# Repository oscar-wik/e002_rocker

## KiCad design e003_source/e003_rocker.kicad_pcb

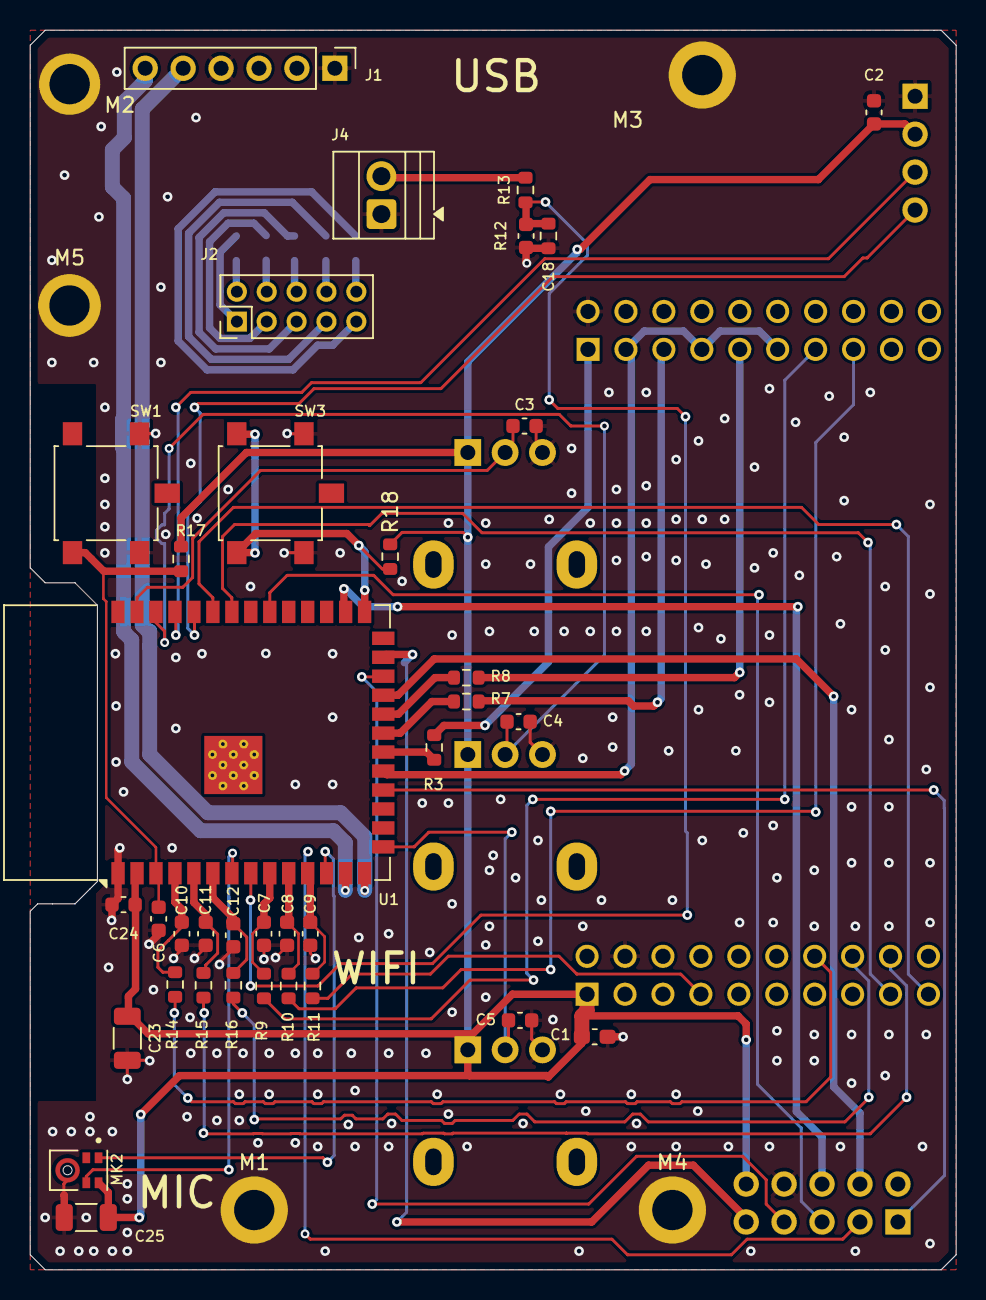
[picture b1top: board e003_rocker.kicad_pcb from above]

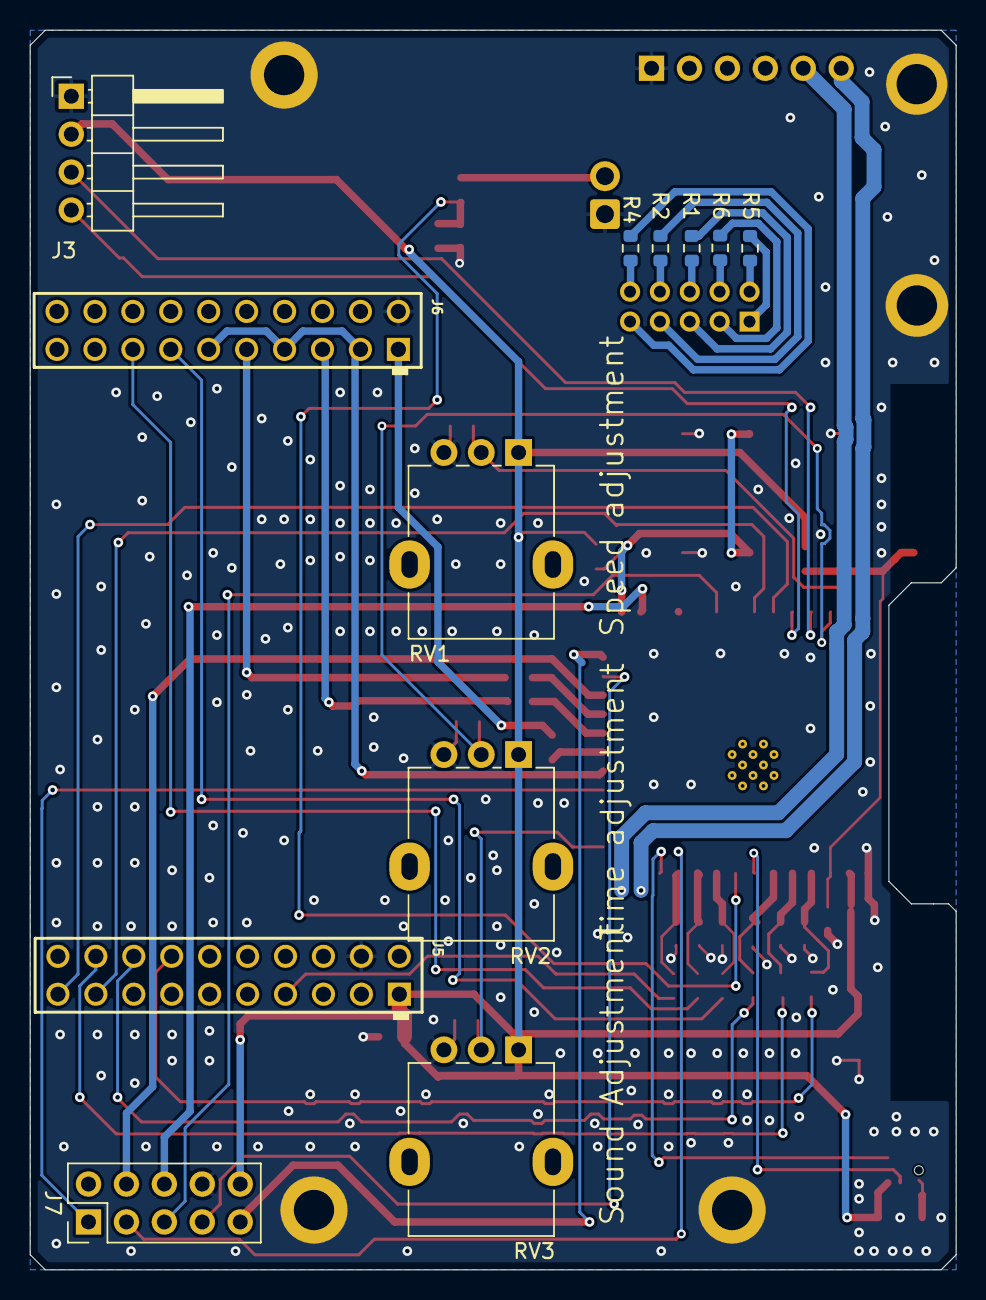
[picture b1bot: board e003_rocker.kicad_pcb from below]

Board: 2 copper layers, 62.0 x 83.0 mm, 53 parts (12 on the bottom side), 52 nets.

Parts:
C1: CL10A105KB8NNNC; C_0603_1608Metric_Pad1.08x0.95mm_HandSolder
C2, C3, C4, C5: 100NF_0201_10V_X7R; C_0603_1608Metric
C6, C18, C24: 1UF 0603 16V X7R; C_0603_1608Metric
C7, C8, C9, C10, C11, C12: 220PF 0603 50V C0G; C_0603_1608Metric
C23: 10UF_1206_35V_X5R; C_1206_3216Metric
C25: 100NF_0201_10V_X7R; C_1206_3216Metric
J1: Conn_01x06_Pin; PinHeader_1x06_P2.54mm_Vertical
J2: Conn_02x05_Odd_Even; PinHeader_2x05_P2.00mm_Vertical
J3: Conn_01x04; PinHeader_1x04_P2.54mm_Horizontal
J4: Conn_01x02_Pin; TerminalBlock_Xinya_XY308-2.54-2P_1x02_P2.54mm_Horizontal
J5, J6: SSQ-110-03-G-D; Samtec_SSQ-110-03-x-D
J7: Conn_02x05_Odd_Even; PinHeader_2x05_P2.54mm_Vertical
M1, M2, M3, M4, M5: CONN_M4_MOUNT; MountingHole_2.7mm_M2.5_ISO7380_Pad
MK2: IC_KNOWLES_SPH0141LM4H-1; MIC_KNOWLES_SPH0641LM4H-1
R1, R2, R4, R5, R6: 1K 0603; R_0603_1608Metric
R3, R7, R8, R9, R10, R11, R14, R15, R16: 100R 0603; R_0603_1608Metric
R12, R18: 10K 0603; R_0603_1608Metric
R13: 100K 0603; R_0603_1608Metric
R17: 5.6K 0603; R_0603_1608Metric
RV1, RV2, RV3: R_Potentiometer; Potentiometer_Alpha_RD901F-40-00D_Single_Vertical
SW1, SW3: BTN_OMRON_B3S-1100P; SW_SPST_B3S-1100
U1: ESP32-S3-WROOM-1-N8R2; ESP32-S3-WROOM-1

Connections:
+3V3: C1.1, C2.1, C23.1, C24.1, C25.1, J3.2, J5.1, J7.10, MK2.5 (VDD), R17.2, R18.2, RV1.1, RV2.1, RV3.1, U1.2 (3V3)
/DRV-HIZ_N: J6.3, J6.7, J6.11, U1.19 (IO11)
/DRV-INHA: J6.1, R3.2
/DRV-INHB: J6.5, R7.2
/DRV-INHC: J6.9, R8.2
/ESP-RXD: J3.4, U1.36 (RXD0)
/ESP-TXD: J3.3, U1.37 (TXD0)
/ESP_EN: C6.1, R17.1, SW1.1 (B), U1.3 (EN)
/ESP_IO0: R18.1, SW3.1 (B), U1.27 (IO0)
/GIO10: J7.1, U1.18 (IO10)
/GIO21: J7.4, U1.23 (IO21)
/GIO35: J7.6, U1.28 (IO35)
/GIO39: J7.5, U1.32 (IO39)
/GIO47: J7.7, U1.24 (IO47)
/GIO48: J7.9, U1.25 (IO48)
/HALL-A: J6.13, R9.2
/HALL-B: J6.15, R10.2
/HALL-C: J5.7, R11.2
/ISENS_A: J5.14, R14.1
/ISENS_B: J5.16, R16.1
/ISENS_C: J5.18, R15.1
/MIC_CLK: MK2.4 (CLOCK), U1.7 (IO7)
/MIC_DATA: MK2.1 (DATA), U1.12 (IO8)
/PD_5V: J2.10, R4.2
/PD_9V: J2.8, R2.2
/PD_12V: J2.6, R1.2
/PD_15V: J2.4, R6.2
/PD_20V: J2.2, R5.2
/POT_MIC: C5.1, RV3.2, U1.15 (IO3)
/POT_SPEED: C3.1, RV1.2, U1.39 (IO1)
/POT_TIME: C4.1, RV2.2, U1.38 (IO2)
/USB_N: J1.6, U1.13 (IO19)
/USB_P: J1.5, U1.14 (IO20)
/nFAULT: J5.19, U1.35 (IO42)
/nSLEEP: J5.17, U1.34 (IO41)
GND: C1.2, C2.2, C3.2, C4.2, C5.2, C6.2, C7.2, C8.2, C9.2, C10.2, C11.2, C12.2, C18.2, C23.2, C24.2, C25.2, J1.1, J1.4, J3.1, J4.1, J5.4, J6.2, J7.8, M1.1, M2.1, M3.1, M4.1, M5.1, MK2.3_1 (GND), MK2.3_2 (GND), R12.1, RV1.3, RV2.3, RV3.3, SW1.2 (1), SW3.2 (1), U1.1 (GND), U1.40 (GND__1)
unnamed: J2.1, R5.1
unnamed: J2.3, R6.1
unnamed: J2.5, R1.1
unnamed: J2.7, R2.1
unnamed: J2.9, R4.1
unnamed: C10.1, R14.2, U1.4 (IO4)
unnamed: C11.1, R15.2, U1.5 (IO5)
unnamed: C12.1, R16.2, U1.6 (IO6)
unnamed: R3.1, U1.20 (IO12)
unnamed: R7.1, U1.21 (IO13)
unnamed: R8.1, U1.22 (IO14)
unnamed: C7.1, R9.1, U1.9 (IO16)
unnamed: C8.1, R10.1, U1.10 (IO17)
unnamed: C9.1, R11.1, U1.11 (IO18)
VBUS: J4.2, R13.2
VBUS_SENSE: C18.1, R12.2, R13.1, U1.8 (IO15)

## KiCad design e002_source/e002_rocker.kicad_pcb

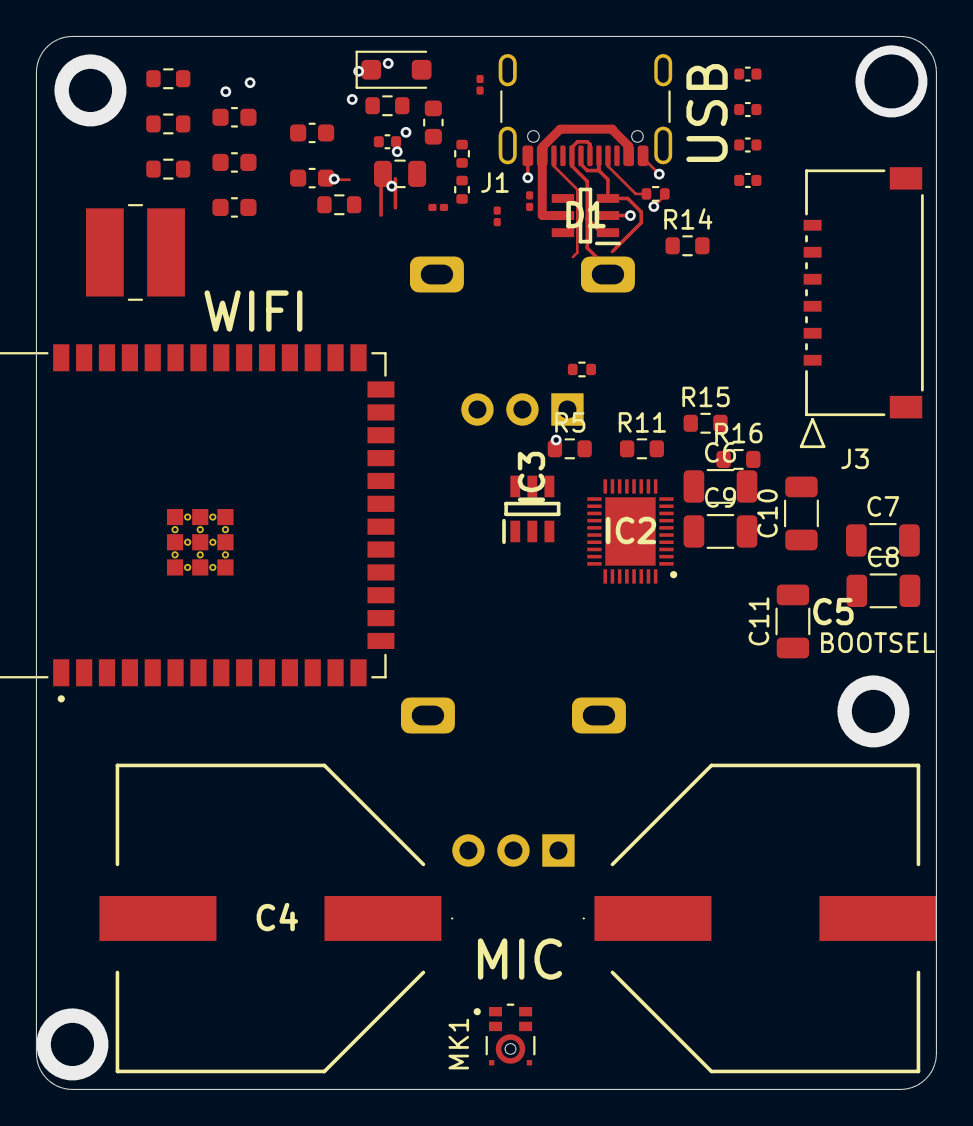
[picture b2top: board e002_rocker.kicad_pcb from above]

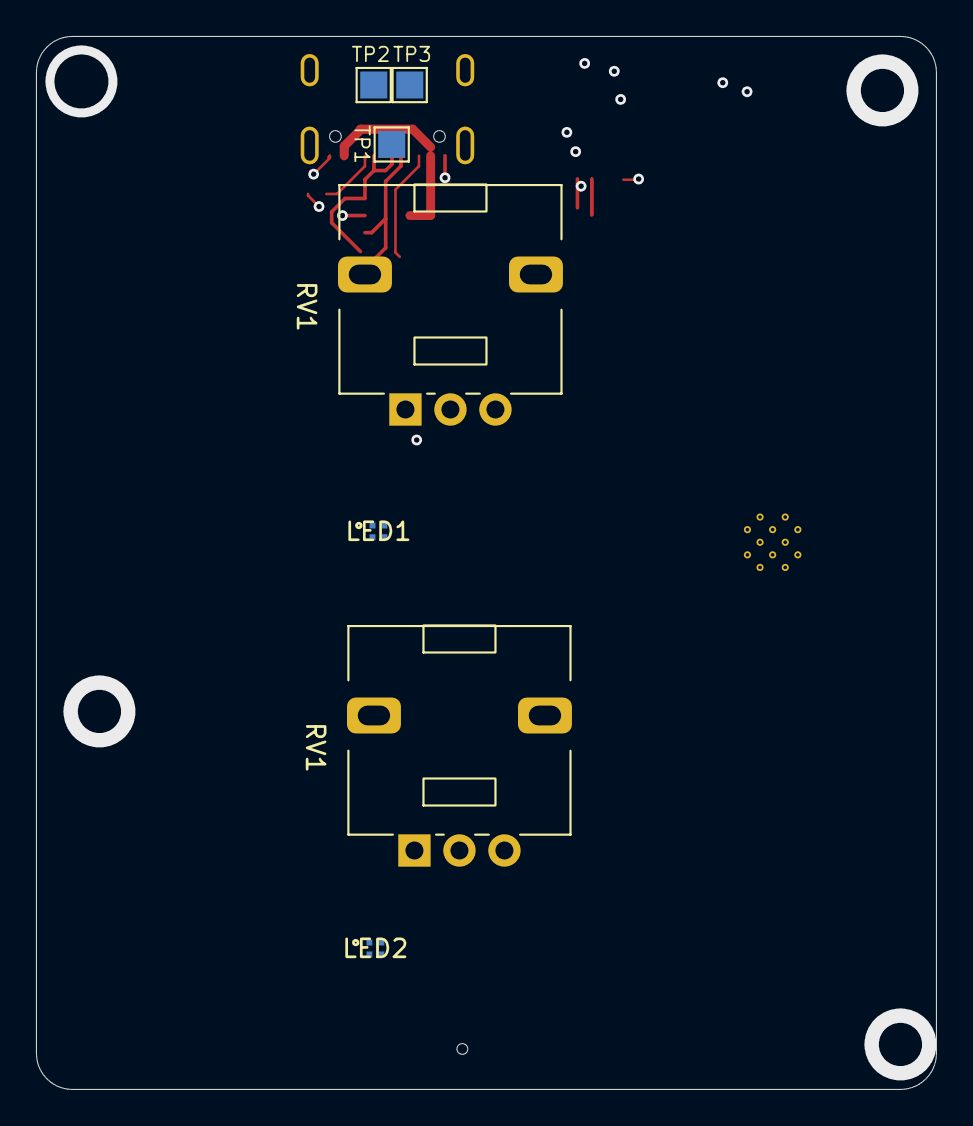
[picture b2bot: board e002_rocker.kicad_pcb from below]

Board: 2 copper layers, 50.0 x 58.5 mm, 54 parts (7 on the bottom side), 33 nets.

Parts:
C1: 4.7UF 0402 10V X7R; C_0402_1005Metric
C2: 1n; C_0201_0603Metric
C3: 10UF_0805_16V_X7R; C_0805_2012Metric
C4, C5: CAPP_PANASONIC_EEV-FK1E222M; CAPP_PANASONIC_EEEFK0J682AM
C6, C7, C8, C9, C10, C11: 10UF_1206_35V_X5R; C_1206_3216Metric
C12, C13, C14: 100NF 0402 25V X7R; C_0402_1005Metric
C15: 1UF 0603 16V X7R; C_0603_1608Metric
C16: 4.7NF 0603 100V X7R; C_0603_1608Metric
C17: 2.2UF 0402 16V X5R; C_0402_1005Metric
C18: 100NF_0201_10V_X7R; C_0201_0603Metric
C19, C20, C21: 47PF 0603 50V C0G; C_0603_1608Metric
D1: PRTR5V0U4D,125; SOT95P275X110-6N
D2: PMEG6010ELR; D_SOD-123F
IC2: DRV8317HREER; QFN40P400X500X80-37N-D
IC3: SOT95P280X125-6N
J1: USB_C_Receptacle_USB2.0_16P; USB_C_Receptacle_GCT_USB4105-xx-A_16P_TopMnt_Horizontal
J3: 5040500691; CONN_MOLEX_5040500691
L1: INDC_BEAD_BLM18AG601SN1D; L_0603_1608Metric
L3: INDC_TDK_VLCF5028T-220MR71-2; IND_TDK_VLCF5028T-220MR71-2
LED1, LED2: RGB; DIOD_CREE_UHD111A-FKA-C3K23E1L3VG5ZB3Z3
MK1: IC_MIC_TDK_MMICT5837-00-012
R1, R2: 5k1; R_0402_1005Metric
R3: 5k6; R_0201_0603Metric
R4: 10k; R_0201_0603Metric
R5, R6, R7, R8, R9, R10: 0R 0603; R_0603_1608Metric
R11, R14, R16: 330R 0603; R_0603_1608Metric
R12: 1.2M 0402; R_0402_1005Metric
R13: 680K 0402; R_0402_1005Metric
R15: 10K 0603; R_0603_1608Metric
RV1, RV1#2: R_Potentiometer; Potentiometer_Alps_RK09L_Single_Vertical
TP1, TP2, TP3: TestPoint; TestPoint_Pad_1.5x1.5mm
U1: ESP32-S3-WROOM-1-N8R2; IC_EXPIF_ESP32-S3-WROOM-1-N8R2

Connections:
+3V3: C3.1, L3.2, R5.2, R7.2, R9.2, R15.2, U1.2 (3V3)
/DRV-INHA: IC2.23 (INHA), U1.20 (IO12)
/DRV-INHB: IC2.25 (INHB), U1.21 (IO13)
/DRV-INHC: IC2.27 (INHC), U1.22 (IO14)
/DRV_AVDD: C17.1, IC2.22 (AVDD)
/ISENS_A: C21.1, R16.1, U1.4 (IO4)
/ISENS_B: C20.1, R14.1
/ISENS_C: C19.1, R11.1, U1.5 (IO5)
/MOTOR_A: IC2.11 (OUTA_1), IC2.12 (OUTA_2)
/MOTOR_B: IC2.14 (OUTB_1), IC2.15 (OUTB_2)
/MOTOR_C: IC2.17 (OUTC_1), IC2.18 (OUTC_2)
GND: C1.2, C2.2, C3.2, C4.2 (-), C5.2 (-), C6.2, C7.2, C8.2, C9.2, C10.2, C11.2, C12.2, C13.2, C14.2, C17.2, C18.2, C19.2, C20.2, C21.2, D1.2 (GND), IC2.10 (PGND_1), IC2.13 (PGND_2), IC2.16 (PGND_3), IC2.19 (PGND_4), IC2.21 (AGND), IC2.37 (GND), J1.A1 (GND), J1.A12 (GND), J1.B1 (GND), J1.B12 (GND), J1.S1 (SHIELD), R1.2, R2.2, R4.2, R6.1, R8.1, R10.1, R13.1, TP1.1, U1.1 (GND), U1.40 (GND__1), U1.41_1 (GND__2), U1.41_2 (GND__3), U1.41_3 (GND__4), U1.41_4 (GND__5), U1.41_5 (GND__6), U1.41_6 (GND__7), U1.41_7 (GND__8), U1.41_8 (GND__9), U1.41_9 (GND__10)
GPIO24: R3.2, R4.1
unnamed: C4.1 (+), C5.1 (+), C6.1, C7.1, C8.1, C9.1, C10.1, C11.1, C13.1, C14.1, C15.1, IC2.7 (VIN_AVDD), IC2.8 (VM_1), IC2.9 (VM_2), IC2.20 (VM_3)
unnamed: C15.2, IC2.6 (CP)
unnamed: C16.1, IC2.5 (CPH)
unnamed: C16.2, IC2.4 (CPL)
unnamed: C12.1, IC2.33 (CSAREF)
unnamed: IC2.29 (GAIN), R5.1, R6.2
unnamed: IC2.31 (MODE), R9.1, R10.2
unnamed: IC2.2 (NFAULT), R15.1
unnamed: IC2.30 (SLEW), R7.1, R8.2
unnamed: IC2.36 (SOA), R16.2
unnamed: IC2.35 (SOB), R14.2
unnamed: IC2.34 (SOC), R11.2
unnamed: IC3.6 (SW), L3.1
unnamed: C1.1, IC3.5 (VIN), L1.2
unnamed: J1.A5 (CC1), R1.1
unnamed: J1.B5 (CC2), R2.1
USB_DM: D1.3 (I/O2), J1.A7 (D-), J1.B7 (D-), TP2.1
USB_DP: D1.1 (I/O1), J1.A6 (D+), J1.B6 (D+), TP3.1
VBUS: C2.1, D1.5 (VCC), D2.2 (A), J1.A4 (VBUS), J1.A9 (VBUS), J1.B4 (VBUS), J1.B9 (VBUS), R3.1, R12.2
VBUS_SENSE: C18.1, R12.1, R13.2

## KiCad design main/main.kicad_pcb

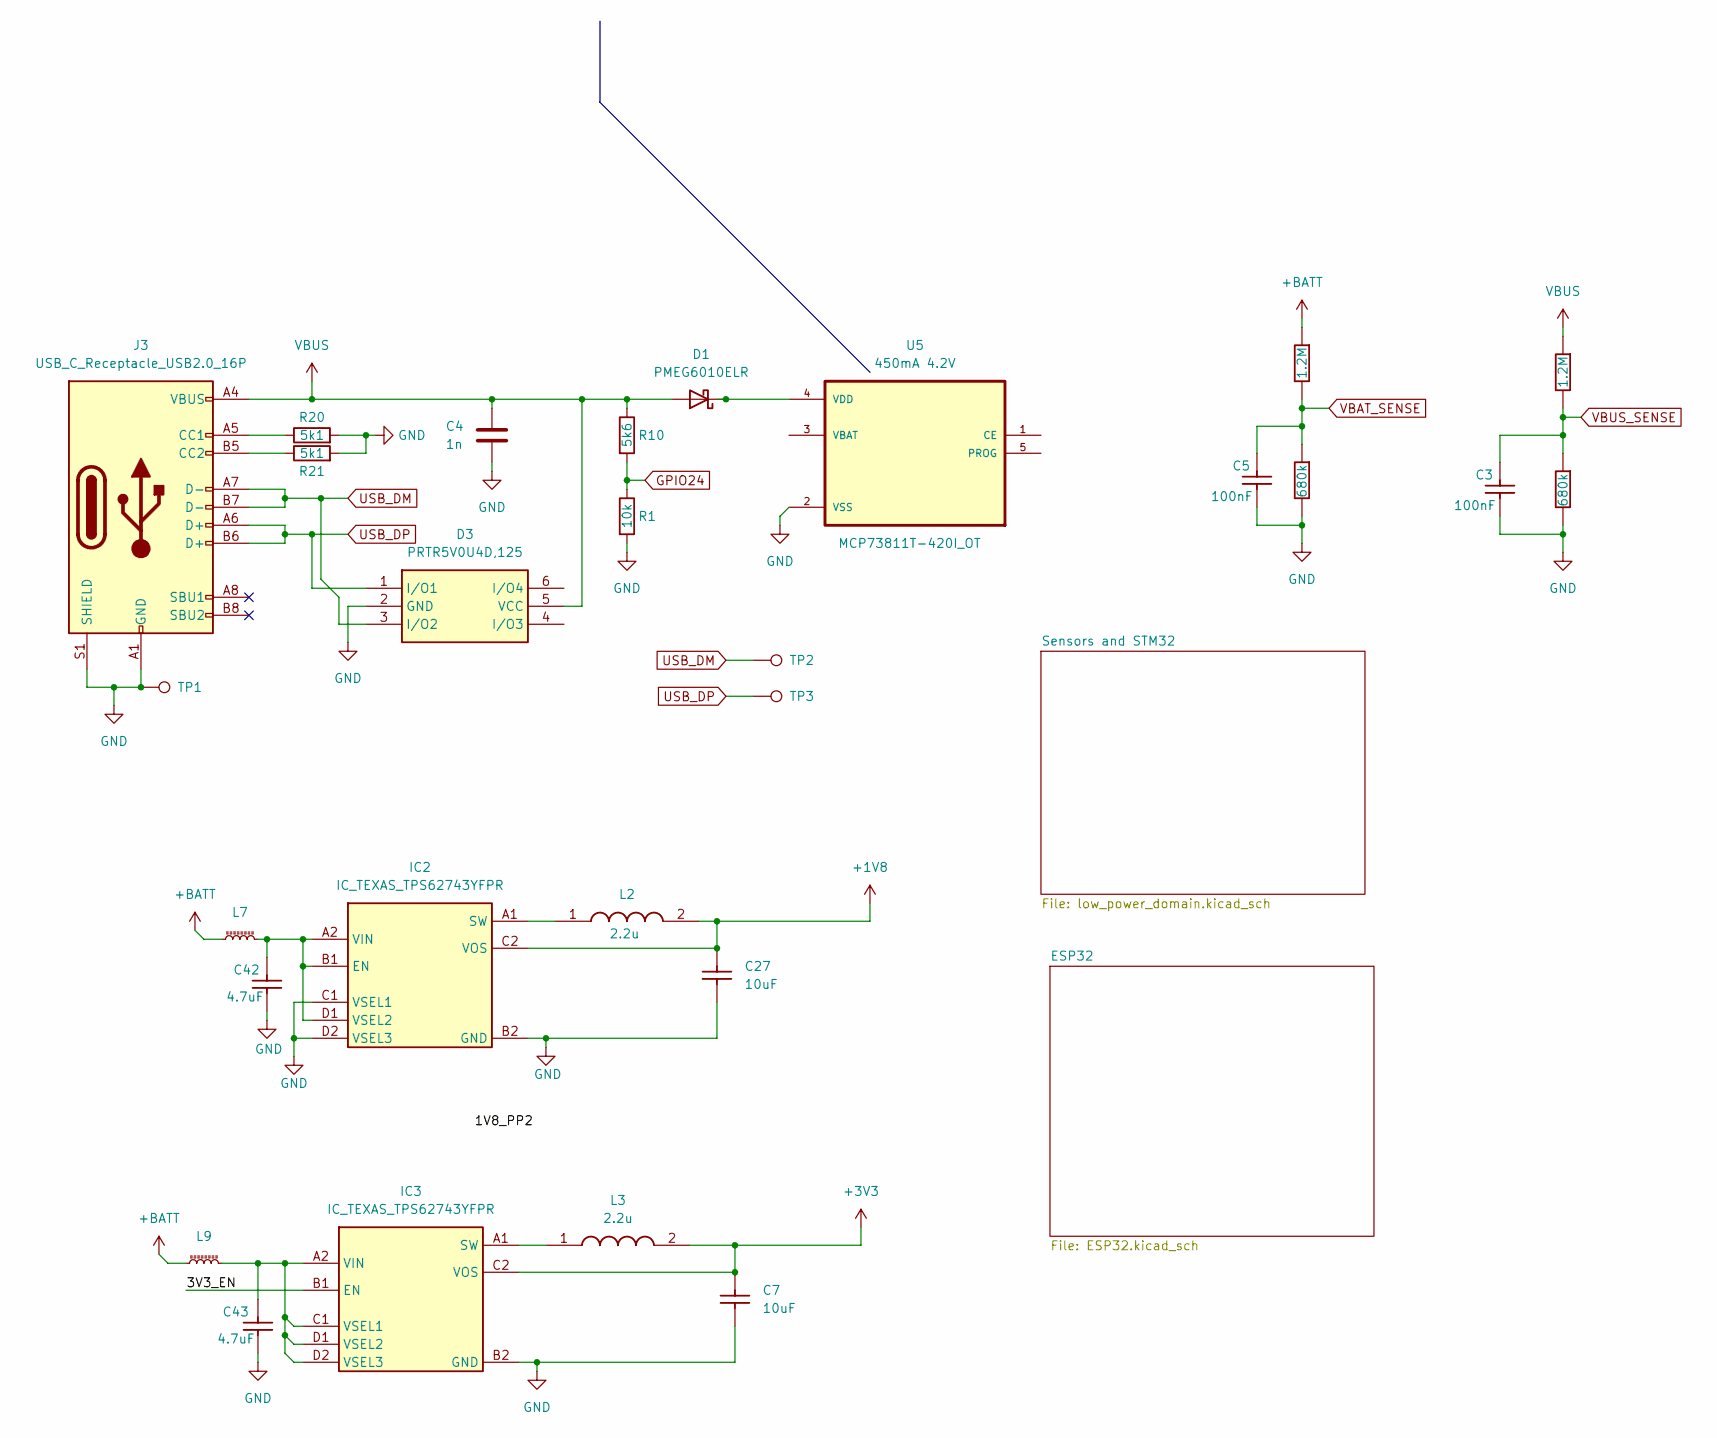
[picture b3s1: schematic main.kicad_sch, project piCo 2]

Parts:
C3, C5: 100NF_0201_10V_X7R; C_0201_0603Metric; Voltage 0V
C4: 1n; C_0201_0603Metric
C7, C27: 10UF_0805_16V_X7R; C_0805_2012Metric
C42, C43: 4.7UF 0402 10V X7R; C_0402_1005Metric; Voltage 0V
D1: PMEG6010ELR; D_SOD-123F
D3: PRTR5V0U4D,125; SOT95P275X110-6N; mpn Nexperia
IC2, IC3: IC_TEXAS_TPS62743YFPR; BGA8C40P2X4_87X156X53; mpn TPS627431YFPR
J3: USB_C_Receptacle_USB2.0_16P; USB_C_Receptacle_GCT_USB4105-xx-A_16P_TopMnt_Horizontal
L2, L3: 2.2u; IND_MURATA_DFE201610P-2R2M=P2; mpn DFE201610P-2R2M=P2
L7, L9: INDC_BEAD_BLM18AG601SN1D; L_0603_1608Metric; mpn BLM18AG601SN1D
R1: 10k; R_0201_0603Metric
R5, R7: 1.2M 0402; R_0402_1005Metric
R6, R9: 680K 0402; R_0402_1005Metric
R10: 5k6; R_0201_0603Metric
R20, R21: 5k1; R_0402_1005Metric
TP1, TP2, TP3: TestPoint; TestPoint_Pad_1.5x1.5mm
U5: 450mA 4.2V; SOT95P280X145-5N; mpn MCP73811T-420I_OT

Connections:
+1V8: C27.1, IC2.C2 (VOS), L2.2; also elsewhere on the board
+3V3: C7.1, IC3.C2 (VOS), L3.2; also elsewhere on the board
+BATT: L7.1, L9.1, R7.2; also elsewhere on the board
/3V3_EN: IC3.B1 (EN)
GND: C3.2, C4.2, C5.2, C7.2, C27.2, C42.2, C43.2, D3.2 (GND), IC2.B2 (GND), IC2.C1 (VSEL1), IC2.D2 (VSEL3), IC3.B2 (GND), J3.A1 (GND), J3.A12 (GND), J3.B1 (GND), J3.B12 (GND), J3.S1 (SHIELD), R1.2, R6.1, R9.1, R20.2, R21.2, TP1.1, U5.2 (VSS); also elsewhere on the board
GPIO24: R1.1, R10.2
unnamed: D1.1 (K), U5.4 (VDD)
unnamed: C42.1, IC2.A2 (VIN), IC2.B1 (EN), IC2.D1 (VSEL2), L7.2
unnamed: IC2.A1 (SW), L2.1
unnamed: IC3.A1 (SW), L3.1
unnamed: C43.1, IC3.A2 (VIN), IC3.C1 (VSEL1), IC3.D1 (VSEL2), IC3.D2 (VSEL3), L9.2
unnamed: J3.A5 (CC1), R20.1
unnamed: J3.B5 (CC2), R21.1
USB_DM: D3.3 (I/O2), J3.A7 (D-), J3.B7 (D-), TP2.1; also elsewhere on the board
USB_DP: D3.1 (I/O1), J3.A6 (D+), J3.B6 (D+), TP3.1; also elsewhere on the board
VBAT_SENSE: C5.1, R7.1, R9.2
VBUS: C4.1, D1.2 (A), D3.5 (VCC), J3.A4 (VBUS), J3.A9 (VBUS), J3.B4 (VBUS), J3.B9 (VBUS), R5.2, R10.1
VBUS_SENSE: C3.1, R5.1, R6.2

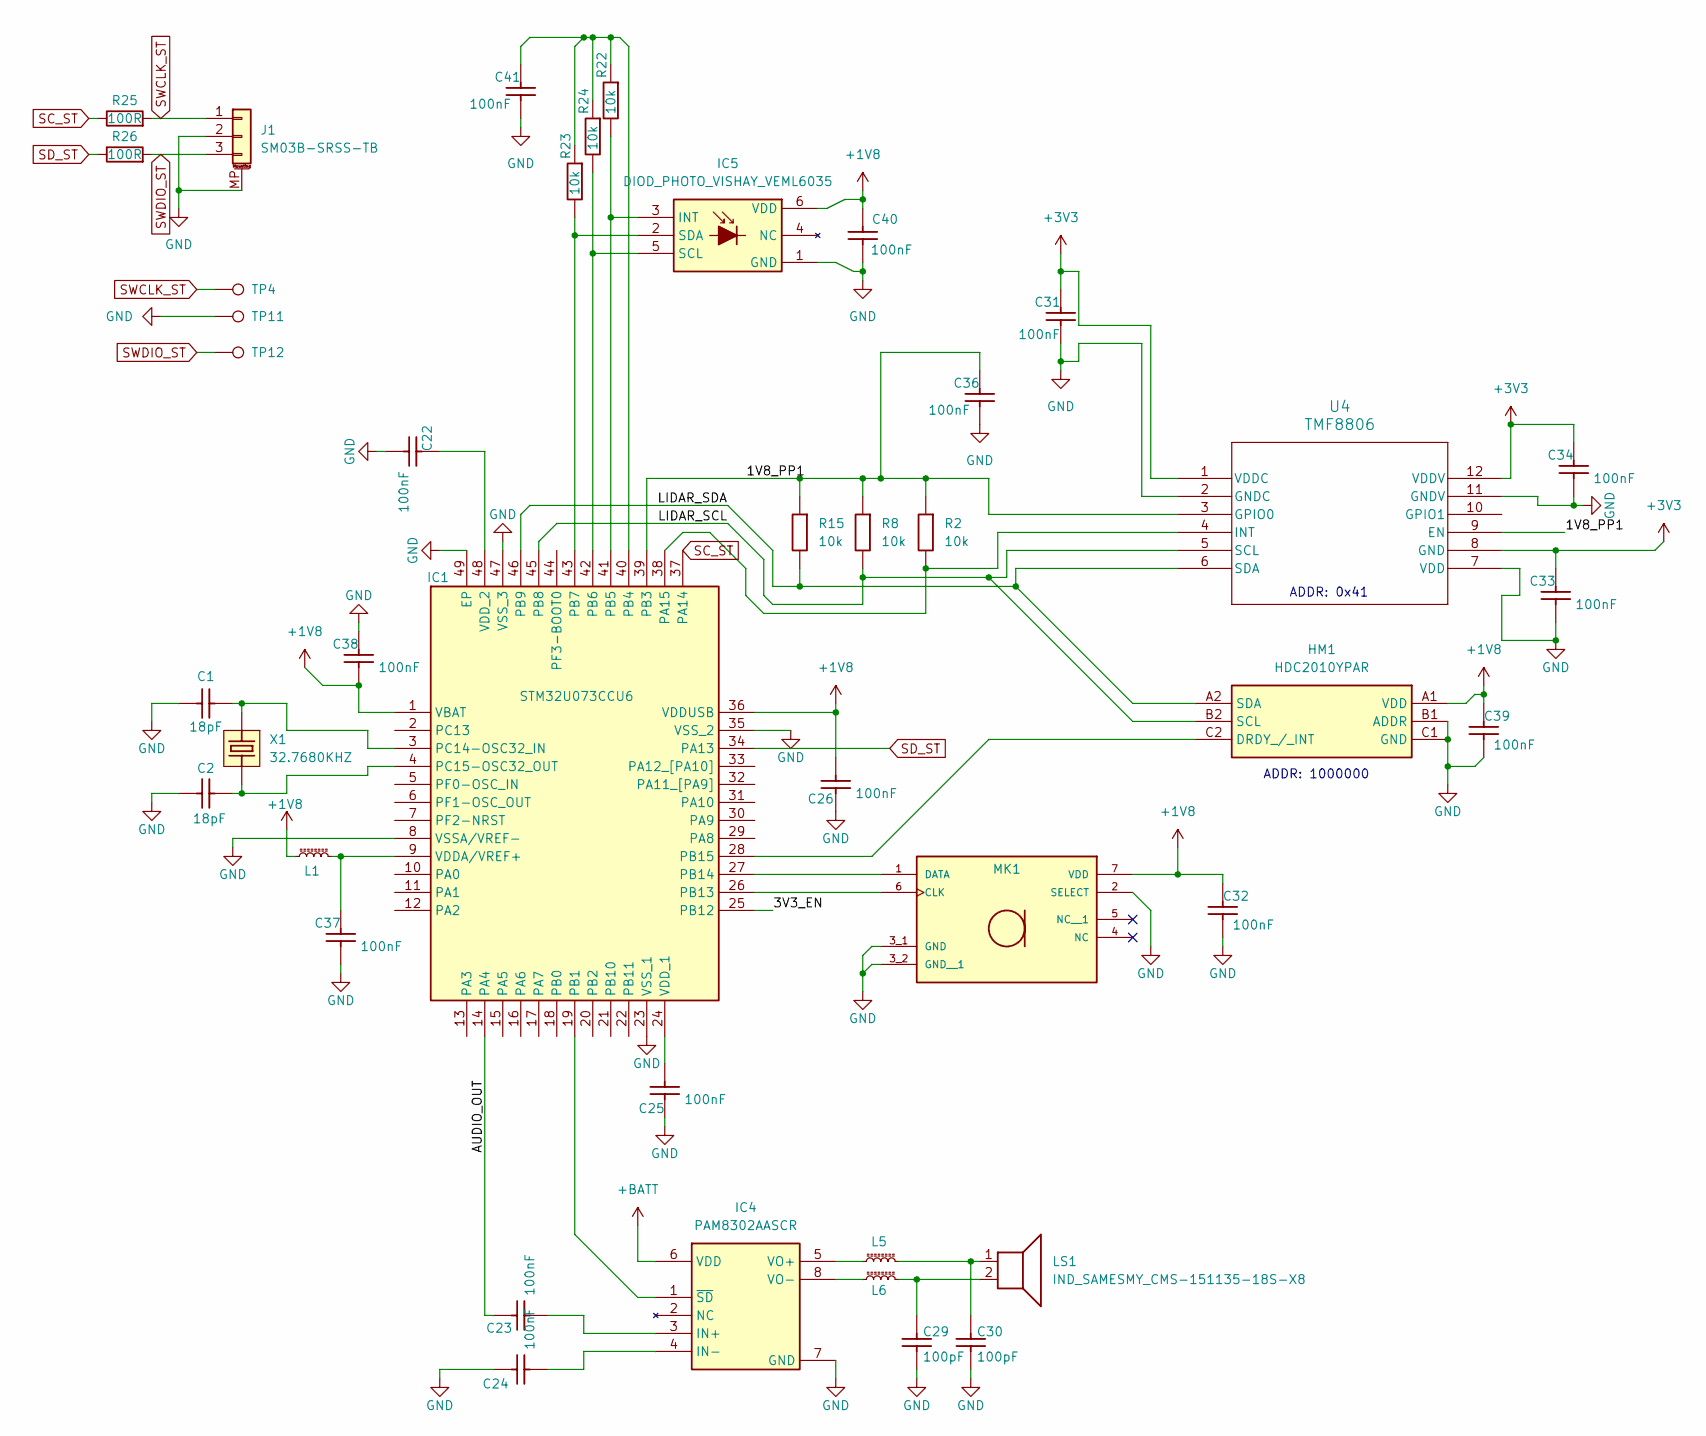
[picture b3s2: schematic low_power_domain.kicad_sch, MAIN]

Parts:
C1, C2: 18PF 0402 50V C0G; C_0402_1005Metric; Voltage 0V
C22, C23, C24, C25, C26, C31, C32, C33, C34, C36, C37, C38, C39, C40, C41: 100NF_0201_10V_X7R; C_0201_0603Metric; Voltage 0V
C29, C30: 100PF 0402 50V C0G; C_0402_1005Metric; Voltage 0V
HM1: HDC2010YPAR; IC_TEXAS_HDC2010YPAR; mpn HDC2010YPAR
IC1: STM32U073CCU6; QFN50P700X700X60-49N-D; Mouser Part Number 511-STM32U073CCU6
IC4: PAM8302AASCR; SOP65P490X110-8N; mpn PAM8302AASCR
IC5: DIOD_PHOTO_VISHAY_VEML6035; mpn VEML6035
J1: SM03B-SRSS-TB; JST_SH_SM03B-SRSS-TB_1x03-1MP_P1.00mm_Horizontal
L1, L5, L6: INDC_BEAD_BLM18AG601SN1D; L_0603_1608Metric; mpn BLM18AG601SN1D
LS1: IND_SAMESMY_CMS-151135-18S-X8; mpn SAMESKY_CMS-151135-18S-X8
MK1: IC_MIC_TDK_MMICT5837-00-012; mpn MMICT5837-00-012
R2, R8, R15, R22, R23, R24: 10K 0402; R_0402_1005Metric
R25, R26: 100R; R_0201_0603Metric
TP4, TP11, TP12: TestPoint; TestPoint_Pad_1.5x1.5mm
U4: TMF8806; IC_OSRAM_TMF8X0X; mpn TMF8806-1AM OLGA12 LF T&RDP
X1: XTAL_ABRACON_ABS07-32.768KHZ-T; XTAL_ABS07-32.768KHZ-T; mpn ABS07-32.768KHZ-T

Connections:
+1V8: C26.1, C32.1, C38.2, C39.1, C40.1, HM1.A1 (VDD), IC1.1 (VBAT), IC1.36 (VDDUSB), IC5.6 (VDD), L1.1, MK1.7 (VDD); also elsewhere on the board
+3V3: C31.1, C33.1, C34.1, U4.1 (VDDC), U4.8 (GND), U4.12 (VDDV); also elsewhere on the board
+BATT: IC4.6 (VDD); also elsewhere on the board
/Sensors and STM32/1V8_PP1: C36.1, IC1.39 (PB3), R2.2, R8.2, R15.2, U4.3 (GPIO0), U4.9 (EN)
/Sensors and STM32/3V3_EN: IC1.25 (PB12)
/Sensors and STM32/AUDIO_OUT: C23.1, IC1.14 (PA4)
/Sensors and STM32/LIDAR_SCL: HM1.B2 (SCL), IC1.45 (PB8), R8.1, U4.5 (SCL)
/Sensors and STM32/LIDAR_SDA: HM1.A2 (SDA), IC1.46 (PB9), R15.1, U4.6 (SDA)
GND: C1.1, C2.1, C22.2, C24.1, C25.2, C26.2, C29.2, C30.2, C31.2, C32.2, C33.2, C34.2, C36.2, C37.2, C38.1, C39.2, C40.2, C41.2, HM1.B1 (ADDR), HM1.C1 (GND), IC1.8 (VSSA/VREF-), IC1.23 (VSS_1), IC1.35 (VSS_2), IC1.47 (VSS_3), IC1.49 (EP), IC4.7 (GND), IC5.1 (GND), J1.2, J1.MP (MountPin), MK1.2 (SELECT), MK1.3_1 (GND), MK1.3_2 (GND__1), TP11.1, U4.2 (GNDC), U4.7 (VDD), U4.11 (GNDV); also elsewhere on the board
unnamed: C29.1, L6.2, LS1.2
unnamed: C30.1, L5.2, LS1.1
unnamed: HM1.C2 (DRDY_/_INT), IC1.28 (PB15)
unnamed: IC1.38 (PA15), R2.1, U4.4 (INT)
unnamed: IC1.19 (PB1), IC4.1 (~SD)
unnamed: C41.1, IC1.40 (PB4), R22.2, R23.2, R24.2
unnamed: IC1.41 (PB5), IC5.3 (INT), R22.1
unnamed: IC1.42 (PB6), IC5.5 (SCL), R24.1
unnamed: IC1.43 (PB7), IC5.2 (SDA), R23.1
unnamed: IC1.26 (PB13), MK1.6 (CLK)
unnamed: IC1.27 (PB14), MK1.1 (DATA)
unnamed: C1.2, IC1.3 (PC14-OSC32_IN), X1.2
unnamed: C2.2, IC1.4 (PC15-OSC32_OUT), X1.1
unnamed: C37.1, IC1.9 (VDDA/VREF+), L1.2
unnamed: C25.1, IC1.24 (VDD_1)
unnamed: C22.1, IC1.48 (VDD_2)
unnamed: C23.2, IC4.3 (IN+)
unnamed: C24.2, IC4.4 (IN-)
unnamed: IC4.5 (VO+), L5.1
unnamed: IC4.8 (VO-), L6.1
SC_ST: IC1.37 (PA14), R25.1
SD_ST: IC1.34 (PA13), R26.1
SWCLK_ST: J1.1, R25.2, TP4.1
SWDIO_ST: J1.3, R26.2, TP12.1

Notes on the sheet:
ADDR: 0x41
ADDR: 1000000

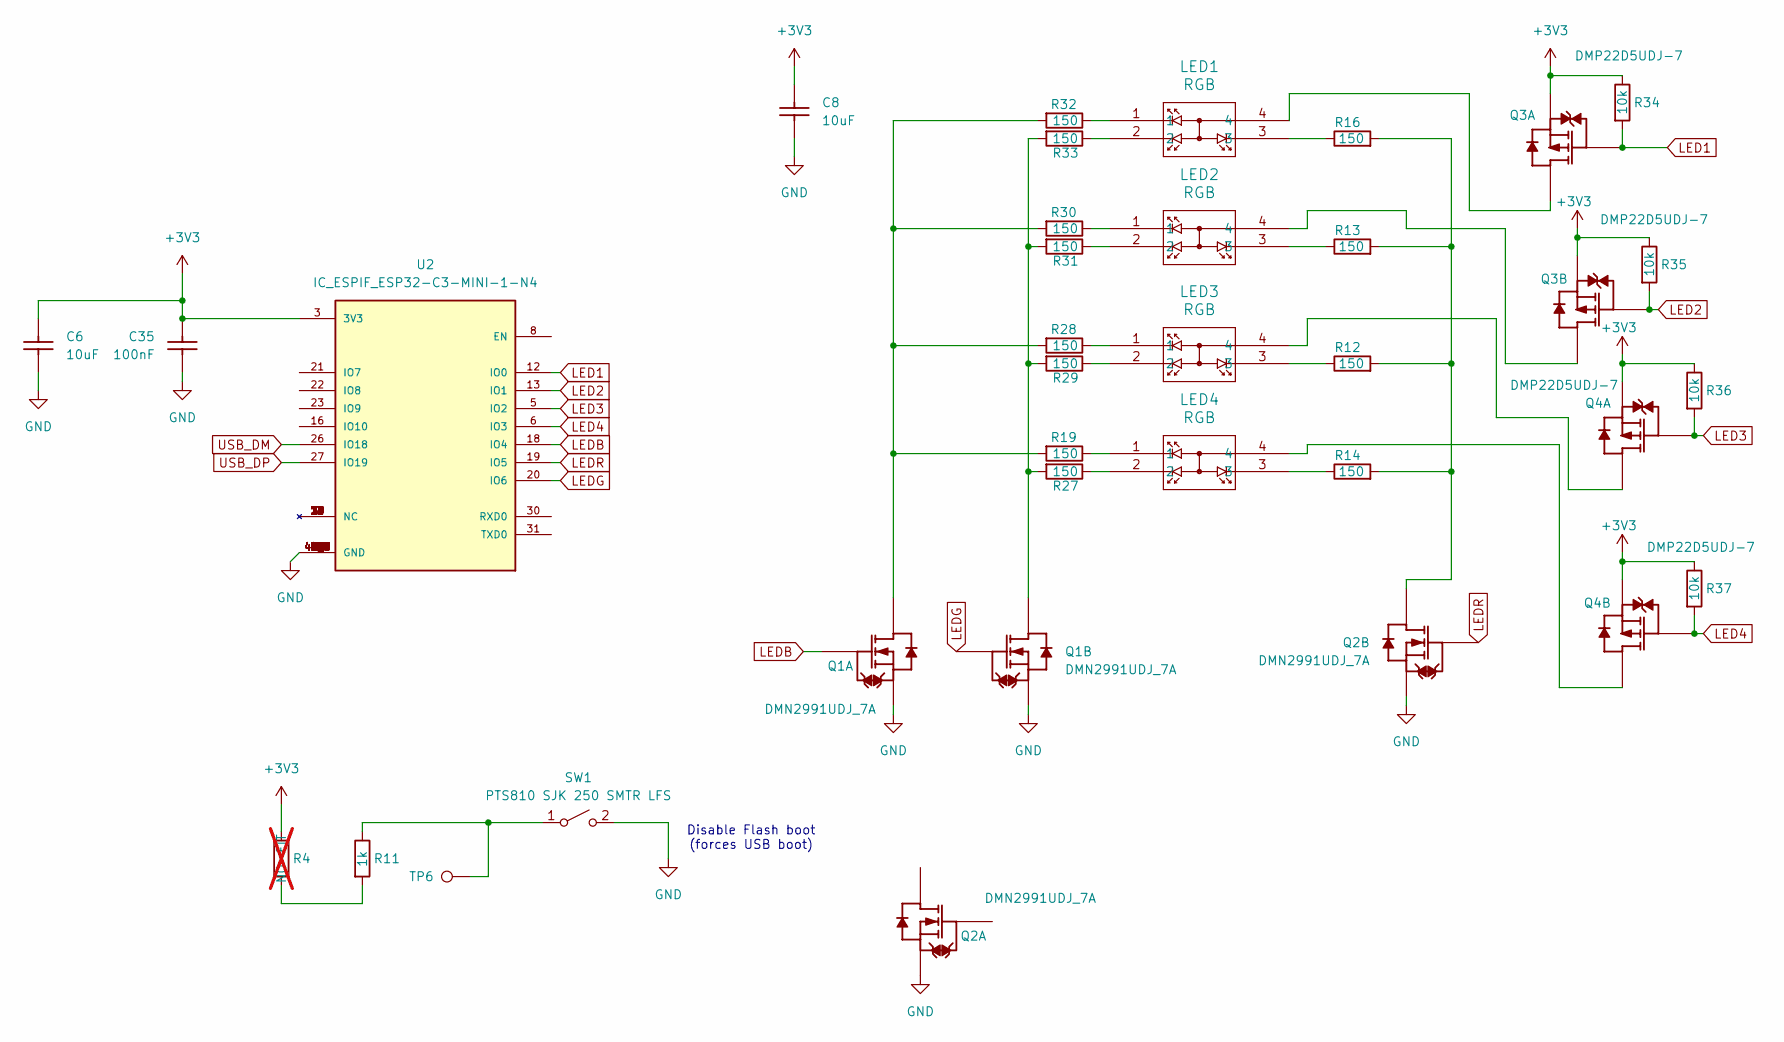
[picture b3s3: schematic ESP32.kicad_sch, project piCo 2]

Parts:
C6, C8: 10UF_0805_16V_X7R; C_0805_2012Metric
C35: 100NF_0201_10V_X7R; C_0201_0603Metric; Voltage 0V
LED1, LED2, LED3, LED4: RGB; DIOD_CREE_UHD111A-FKA-C3K23E1L3VG5ZB3Z3; mpn UHD111A-FKA-C3K23E1L3VG5ZB3Z3
Q1, Q2: TRAN_DIODES_DMN2991UDJ_7A; SOT-963; mpn DMN2991UDJ_7A
Q3, Q4: TRAN_DIODES_DMP22D5UDJ-7; SOT-963; mpn DMP22D5UDJ-7
R4: NO-FIT; R_0201_0603Metric; not fitted
R11: 1k; R_0201_0603Metric
R12, R13, R14, R16, R19, R27, R28, R29, R30, R31, R32, R33: 150; R_0201_0603Metric
R34, R35, R36, R37: 10k; R_0201_0603Metric
SW1: PTS810 SJK 250 SMTR LFS; SW_SPST_PTS810
TP6: TestPoint; TestPoint_Pad_1.5x1.5mm
U2: IC_ESPIF_ESP32-C3-MINI-1-N4; PARTREV v1.0

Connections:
+3V3: C6.1, C8.1, C35.1, Q3.1 (SOURCE), Q3.4 (SOURCE), Q4.1 (SOURCE), Q4.4 (SOURCE), R4.1, R34.1, R35.1, R36.1, R37.1, U2.3 (3V3); also elsewhere on the board
GND: C6.2, C8.2, C35.2, Q1.1 (SOURCE), Q1.4 (SOURCE), Q2.1 (SOURCE), Q2.4 (SOURCE), SW1.2 (B), U2.1 (GND), U2.2 (GND), U2.11 (GND), U2.14 (GND), U2.36 (GND), U2.37 (GND), U2.38 (GND), U2.39 (GND), U2.40 (GND), U2.41 (GND), U2.42 (GND), U2.43 (GND), U2.44 (GND), U2.45 (GND), U2.46 (GND), U2.47 (GND), U2.48 (GND), U2.49_1 (GND), U2.49_2 (GND), U2.49_3 (GND), U2.49_4 (GND), U2.49_5 (GND), U2.49_6 (GND), U2.49_7 (GND), U2.49_8 (GND), U2.49_9 (GND), U2.50 (GND), U2.51 (GND), U2.52 (GND), U2.53 (GND); also elsewhere on the board
LED1: Q3.2 (GATE), R34.2, U2.12 (IO0)
LED2: Q3.5 (GATE), R35.2, U2.13 (IO1)
LED3: Q4.2 (GATE), R36.2, U2.5 (IO2)
LED4: Q4.5 (GATE), R37.2, U2.6 (IO3)
LEDB: Q1.2 (GATE), U2.18 (IO4)
LEDG: Q1.5 (GATE), U2.20 (IO6)
LEDR: Q2.5 (GATE), U2.19 (IO5)
unnamed: LED1.1, R32.1
unnamed: LED1.2, R33.1
unnamed: LED1.3, R16.1
unnamed: LED2.1, R30.1
unnamed: LED2.2, R31.1
unnamed: LED2.3, R13.1
unnamed: LED3.1, R28.1
unnamed: LED3.2, R29.1
unnamed: LED3.3, R12.1
unnamed: LED4.1, R19.1
unnamed: LED4.2, R27.1
unnamed: LED4.3, R14.1
unnamed: Q1.6 (DRAIN), R19.2, R28.2, R30.2, R32.2
unnamed: Q1.3 (DRAIN), R27.2, R29.2, R31.2, R33.2
unnamed: Q2.3 (DRAIN), R12.2, R13.2, R14.2, R16.2
unnamed: LED1.4, Q3.6 (DRAIN)
unnamed: LED2.4, Q3.3 (DRAIN)
unnamed: LED3.4, Q4.6 (DRAIN)
unnamed: LED4.4, Q4.3 (DRAIN)
unnamed: R4.2, R11.2
unnamed: R11.1, SW1.1 (A), TP6.1
USB_DM: U2.26 (IO18); also elsewhere on the board
USB_DP: U2.27 (IO19); also elsewhere on the board

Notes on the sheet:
Disable Flash boot (forces USB boot)

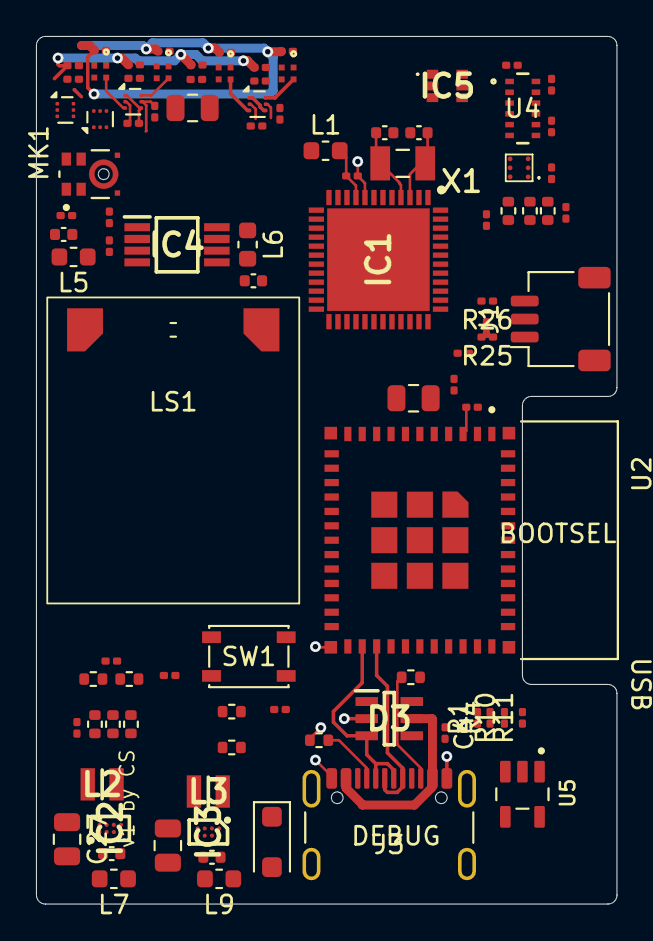
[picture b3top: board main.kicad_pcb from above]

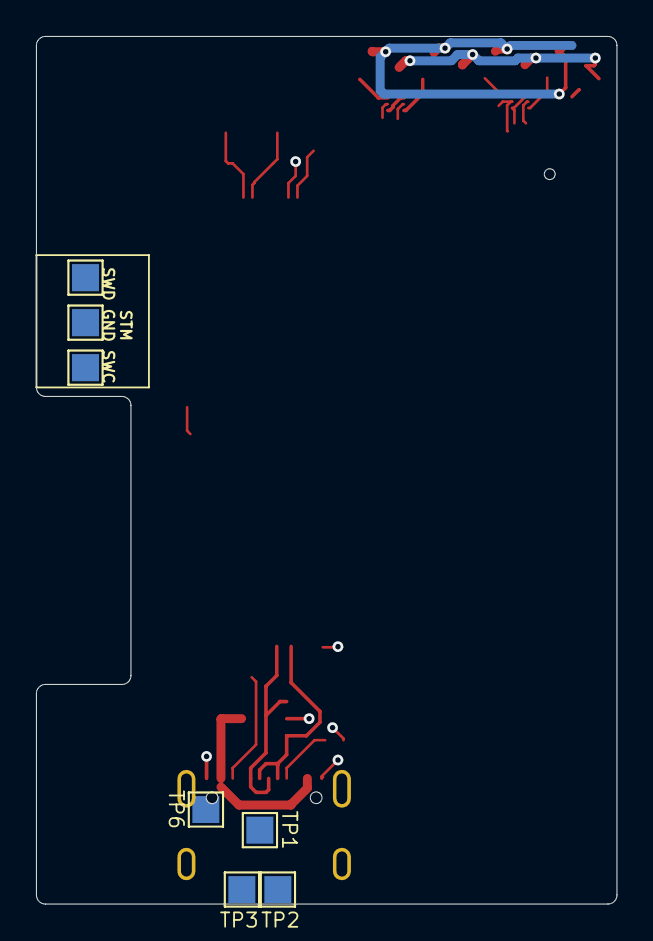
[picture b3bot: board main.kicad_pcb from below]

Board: 2 copper layers, 32.2 x 48.2 mm, 102 parts (7 on the bottom side), 73 nets.

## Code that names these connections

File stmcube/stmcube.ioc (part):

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Mcu.Name=STM32U073CCUx
Mcu.Package=UFQFPN48
Mcu.UserName=STM32U073CCUx
PA4.GPIOParameters=GPIO_Label
PA4.GPIO_Label=AUDIO_OUT
PA4.Signal=COMP_DAC11_group
PB13.GPIOParameters=GPIO_Label
PB13.GPIO_Label=MIC_PDM_SCK
PB13.Mode=RX_Only_Simplex_Unidirect_Master
PB13.Signal=SPI2_SCK
PB14.GPIOParameters=GPIO_Label
PB14.GPIO_Label=MIC_PDM_MISO
PB14.Mode=RX_Only_Simplex_Unidirect_Master
PB14.Signal=SPI2_MISO
PB8.GPIOParameters=GPIO_Label
PB8.GPIO_Label=LIDAR_SCL
PB8.Mode=I2C
PB8.Signal=I2C1_SCL
PB9.GPIOParameters=GPIO_Label
PB9.GPIO_Label=LIDAR_SDA
PB9.Mode=I2C
PB9.Signal=I2C1_SDA
RCC.HSE_VALUE=4000000
RCC.SYSCLKFreq_VALUE=16000000
board=custom

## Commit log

2025-10-13 added first template
2025-10-13 added submodule to template
2025-10-14 merging a pi pico board with low power domain
2025-10-14 last commit with pi-pico still on
2025-10-14 added leds and removed pico, changed outline
2025-10-20 first commit of e002 rocker
2025-11-03 removed STM MCU to optimize cost
2025-11-11 commit after review. version sent to aisler
2026-03-13 before real start of EVT
2026-03-29 first evt to jlc
2026-03-30 pre cleanup
2026-06-09 last data sent to jlc
